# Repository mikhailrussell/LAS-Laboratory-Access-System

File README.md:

# LAS-Laboratory-Access-System-
Current PCB Version: **LAS_V2**
You can find the most recent version of the PCB under /PCB

# User Requirements
|Number/Label	|Requirement|
|----------|------------|
|UR-1	| Allow clients to book particular sessions (time and date). |
|UR-2|	Allow clients to view what the status of laboratory.
|UR-3|	Integrate access control with the current student card for identification.
|UR-4|	Provide access to clients who have been allocated the correct session.
|UR-5|	The status of benches must be physically displayed on the bench.
|UR-6|	The system must be easily scalable.
|UR-7|	The system must be cheap.

# Hardware Functional Requirements

|Number/label	|Requirements	|Acceptance Test Criteria|
|----------|------------|------------|
|FR-1	|Retrieve student's IDs from 125KHz RFID student cards.	|
|FR-2	|Connect to network wirelessly.	|
|FR-3	|Each bench must have LEDs to indicate whether the bench is available, booked or in use.|	
|FR-4	|Each node must be able to activate a 220V relay.	|
|FR-5	|Operate off 12V	|
|FR-6	|Cheap and easily scalable	|

# Software Functional Requirements

|Number/label	|Requirements	|Acceptance Test Criteria|
|----------|------------|------------|
|FR-6|	Site accessible via Wi-Fi (website accessible)	|
FR-7|	Free	|
FR-8|	Client able to book time and date	|
FR-9	|Current lab status is displayed (eg. Current tables free)	|

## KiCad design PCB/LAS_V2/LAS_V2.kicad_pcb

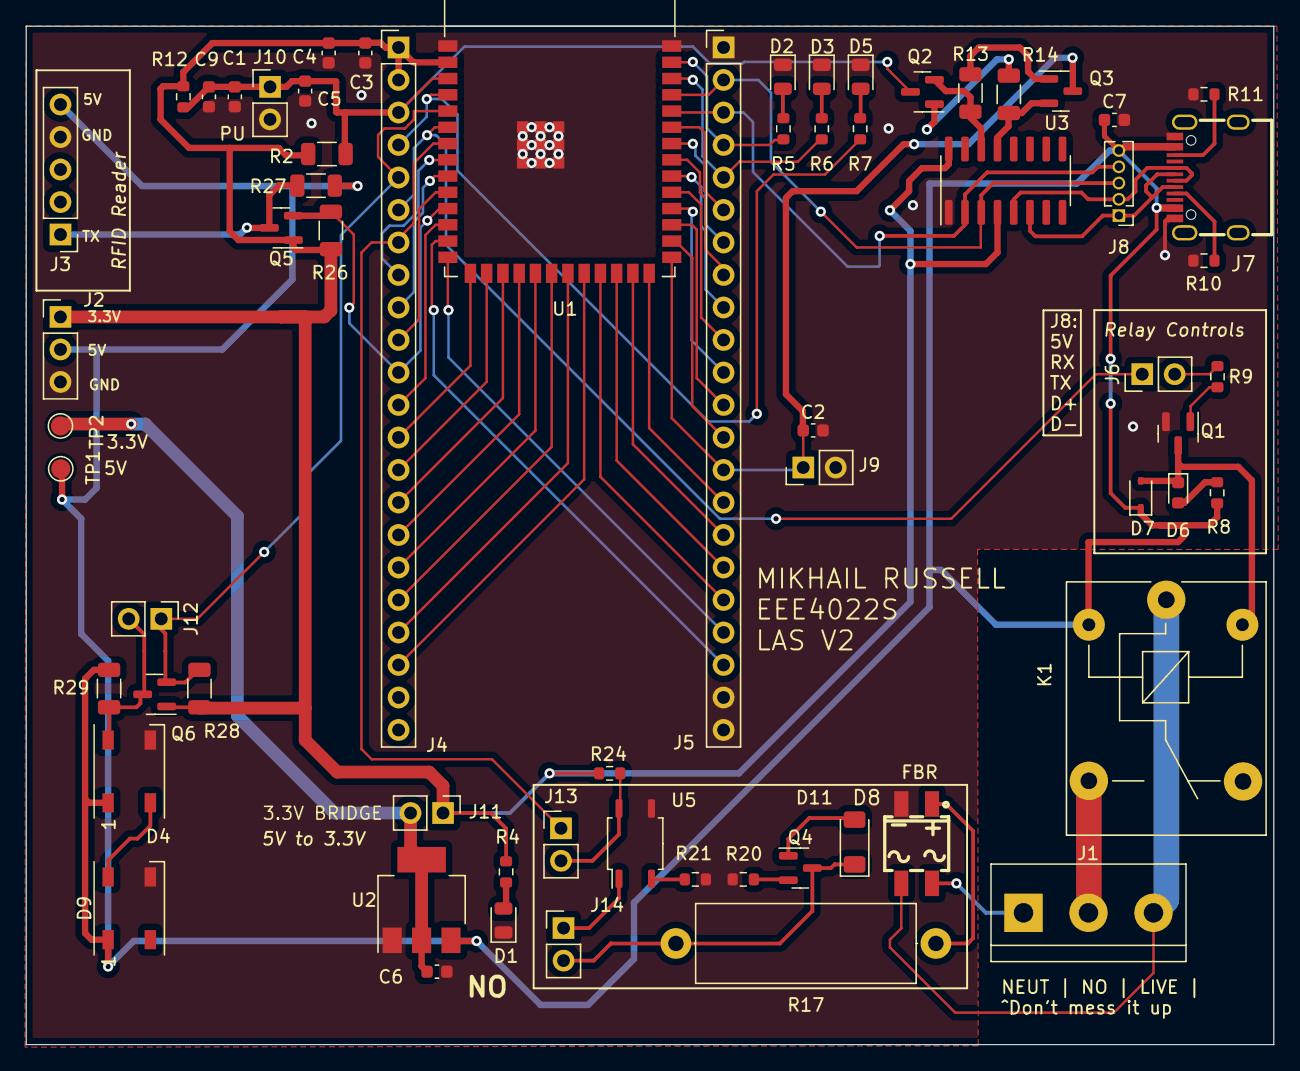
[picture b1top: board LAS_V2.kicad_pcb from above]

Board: 2 copper layers, 97.5 x 79.6 mm, 65 parts (0 on the bottom side), 70 nets.

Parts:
C1: 1uF; C_0603_1608Metric
C2, C4, C5: 0.1uF; C_0603_1608Metric
C3, C6: 10uF; C_0603_1608Metric
C7, C9: 1uF/16V (10%); C_0603_1608Metric
D1, D2: RED LED; LED_0805_2012Metric
D3: YELLOW LED; LED_0805_2012Metric
D4, D9: WS2812B; LED_WS2812B_PLCC4_5.0x5.0mm_P3.2mm
D5: GREEN LED; LED_0805_2012Metric
D6: LED; LED_0603_1608Metric
D7: 1N5819WS; D_SOD-323
D8: MB10S; MBS_L4.7-W3.8-P2.40-LS7.0-TL
D11: ZMMxx; D_MiniMELF
J1: Screw_Terminal_01x03; TerminalBlock_bornier-3_P5.08mm
J2: Conn_01x03_Pin; PinHeader_1x03_P2.54mm_Vertical
J3: Conn_01x05_Socket; PinHeader_1x05_P2.54mm_Vertical
J4, J5: Conn_01x22_Socket; PinHeader_1x22_P2.54mm_Vertical
J6, J9, J10, J11, J12, J13, J14: Conn_01x02_Pin; PinHeader_1x02_P2.54mm_Vertical
J7: USB_C_Receptacle_USB2.0; USB-C_SMD-TYPE-C-31-M-12
J8: Conn_01x05; PinHeader_1x05_P1.27mm_Vertical
K1: SRD-05VDC-SL-C; Relay_SPDT_SANYOU_SRD_Series_Form_C
Q1, Q2, Q3, Q4: MMBT2222A; SOT-23
Q5, Q6: AO3400A; SOT-23
R2, R13, R14, R26, R27, R28, R29: 10k; R_1206_3216Metric
R4, R5, R6, R7, R8, R21: 1k; R_0603_1608Metric
R9: 150; R_0603_1608Metric
R10, R11: 5.1k; R_0603_1608Metric
R12: 10k (1%); R_0603_1608Metric
R17: 47k 3W; R_Axial_DIN0617_L17.0mm_D6.0mm_P20.32mm_Horizontal
R20, R24: 2.2k; R_0603_1608Metric
TP1, TP2: TestPoint; TestPoint_Pad_D1.5mm
U1: ESP32-S3-WROOM-1
U2: AMS1117-3.3; SOT-223-3_TabPin2
U3: CH340C; SOIC-16_3.9x9.9mm_P1.27mm
U5: EL357N; SOP-4_3.8x4.1mm_P2.54mm

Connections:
/+3.3V: C3.1, C4.1, J2.1, J4.1, J4.2, J11.1, Q5.1 (G), Q6.1 (G), R2.1, R4.1, R12.1, R24.2, R26.1, R28.1, U1.2 (3V3), U3.4 (V3), U3.16 (VCC)
/AC_Mon_1: J4.7, J13.1, U1.7 (GPIO7/TOUCH7/ADC1_CH6)
/BOOT_SEL: C2.1, J5.14, J9.1, Q3.3 (C), U1.27 (GPIO0/BOOT)
/CHIP_PU: C1.1, C5.1, C9.1, J4.3, J10.1, Q2.3 (C), R2.2, R12.2, U1.3 (EN)
/DIN_3.3: J4.5, J12.1, Q6.2 (S), R28.2, U1.5 (GPIO5/TOUCH5/ADC1_CH4)
/GPIO1: J5.4, R5.1, U1.39 (GPIO1/TOUCH1/ADC1_CH0)
/GPIO2: J5.5, R6.1, U1.38 (GPIO2/TOUCH2/ADC1_CH1)
/GPIO3: J4.13, U1.15 (GPIO3/TOUCH3/ADC1_CH2)
/GPIO4: J4.4, R7.1, U1.4 (GPIO4/TOUCH4/ADC1_CH3)
/GPIO6: J4.6, J6.1, U1.6 (GPIO6/TOUCH6/ADC1_CH5)
/GPIO8: J4.12, U1.12 (GPIO8/TOUCH8/ADC1_CH7/SUBSPICS1)
/GPIO9: J4.15, U1.17 (GPIO9/TOUCH9/ADC1_CH8/FSPIHD/SUBSPIHD)
/GPIO10: J4.16, U1.18 (GPIO10/TOUCH10/ADC1_CH9/FSPICS0/FSPIIO4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)
/GPIO11: J4.17, U1.19 (GPIO11/TOUCH11/ADC2_CH0/FSPID/FSPIIO5/S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)
/GPIO12: J4.18, U1.20 (GPIO12/TOUCH12/ADC2_CH1/FSPICLK/FSPIIO6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)
/GPIO13: J4.19, U1.21 (GPIO13/TOUCH13/ADC2_CH2/FSPIQ/FSPIIO7/S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)
/GPIO14: J4.20, U1.22 (GPIO14/TOUCH14/ADC2_CH3/FSPIWP/FSPIDQS/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)
/GPIO15: J4.8, U1.8 (GPIO15/U0RTS/ADC2_CH4/XTAL_32K_P)
/GPIO16: J4.9, U1.9 (GPIO16/U0CTS/ADC2_CH5/XTAL_32K_N)
/GPIO17: J4.10, U1.10 (GPIO17/U1TXD/ADC2_CH6)
/GPIO18: J4.11, Q5.2 (S), R26.2, U1.11 (GPIO18/U1RXD/ADC2_CH7/CLK_OUT3)
/GPIO19: J5.20, U1.13 (GPIO19/U1RTS/ADC2_CH8/CLK_OUT2/USB_D-)
/GPIO20: J5.19, U1.14 (GPIO20/U1CTS/ADC2_CH9/CLK_OUT1/USB_D+)
/GPIO21: J5.18, U1.23 (GPIO21)
/GPIO35: J5.13, U1.28 (SPIIO6/GPIO35/FSPID/SUBSPID)
/GPIO36: J5.12, U1.29 (SPIIO7/GPIO36/FSPICLK/SUBSPICLK)
/GPIO37: J5.11, U1.30 (SPIDQS/GPIO37/FSPIQ/SUBSPIQ)
/GPIO38: J5.10, U1.31 (GPIO38/FSPIWP/SUBSPIWP)
/GPIO39: J5.9, U1.32 (MTCK/GPIO39/CLK_OUT3/SUBSPICS1)
/GPIO40: J5.8, U1.33 (MTDO/GPIO40/CLK_OUT2)
/GPIO41: J5.7, U1.34 (MTDI/GPIO41/CLK_OUT1)
/GPIO42: J5.6, U1.35 (MTMS/GPIO42)
/GPIO45: J5.15, U1.26 (GPIO45)
/GPIO46: J4.14, U1.16 (GPIO46)
/GPIO47: J5.17, U1.24 (GPIO47/SPICLK_P/SUBSPICLK_P_DIFF)
/GPIO48: J5.16, U1.25 (GPIO48/SPICLK_N/SUBSPICLK_N_DIFF)
/LEDs/DIN: D4.4 (DIN), J12.2, Q6.3 (D), R29.2
/LIVE: D8.3, J1.3, K1.1
/N01: J1.2, K1.3
/NEUTRAL: D8.4, J1.1
/RXD0: J5.3, J8.4, U1.36 (U0RXD/GPIO44/CLK_OUT2), U3.2 (TXD)
/TXD0: J5.2, J8.3, U1.37 (U0TXD/GPIO43/CLK_OUT1), U3.3 (RXD)
/TX_RFID: J3.1, Q5.3 (D), R27.2
/USB Interface/DTR: Q3.2 (E), R14.1, U3.13 (~DTR)
/USB Interface/RTS: Q2.2 (E), R13.1, U3.14 (~RTS)
/VCC_5V: C7.1, D4.1 (VDD), D7.1 (K), D9.1 (VDD), J2.2, J3.5, J7.A4 (VBUS), J7.A9 (VBUS), J7.B4 (VBUS), J7.B9 (VBUS), J8.5, K1.2, R8.1, R27.1, R29.1, TP1.1, U2.3 (VI)
GND: C1.2, C2.2, C3.2, C4.2, C5.2, C6.2, C7.2, C9.2, D1.1 (K), D2.1 (K), D3.1 (K), D4.3 (VSS), D5.1 (K), D8.2 (-), D9.3 (VSS), J2.3, J3.4, J5.1, J5.21, J5.22, J7.A1 (GND), J7.A12 (GND), J7.B1 (GND), J7.B12 (GND), J9.2, J10.2, Q1.2 (E), R10.2, R11.2, R20.1, R21.1, U1.1 (GND), U1.40 (GND), U1.41 (GND), U2.1 (GND), U3.1 (GND), U5.3
unnamed: D1.2 (A), R4.2
unnamed: D2.2 (A), R5.2
unnamed: D3.2 (A), R6.2
unnamed: D4.2 (DOUT), D9.4 (DIN)
unnamed: D5.2 (A), R7.2
unnamed: D6.2 (A), R8.2
unnamed: D6.1 (K), D7.2 (A), K1.5, Q1.3 (C)
unnamed: D8.1 (+), R17.1
unnamed: D11.2 (A), Q4.1 (B)
unnamed: D11.1 (K), J14.2, Q4.3 (C), R17.2
unnamed: J6.2, R9.1
unnamed: J7.A5 (CC1), R10.1
unnamed: J7.B5 (CC2), R11.1
unnamed: J7.A7 (D-), J7.B7 (D-), J8.1, U3.6 (UD-)
unnamed: J7.A6 (D+), J7.B6 (D+), J8.2, U3.5 (UD+)
unnamed: C6.1, J11.2, TP2.1, U2.2 (VO)
unnamed: J13.2, R24.1, U5.4
unnamed: J14.1, U5.1
unnamed: Q1.1 (B), R9.2
unnamed: Q2.1 (B), R14.2
unnamed: Q3.1 (B), R13.2
unnamed: Q4.2 (E), R20.2
unnamed: R21.2, U5.2

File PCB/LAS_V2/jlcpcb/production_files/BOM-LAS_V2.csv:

Comment,Designator,Footprint,LCSC
0.1uF,"C2,C4,C5",C_0603_1608Metric,C14663
1uF,"C1,C7,C9",C_0603_1608Metric,C15849
10k,"R13,R14,R2,R26,R27,R28,R29",R_1206_3216Metric,C17902
1N5819WS,D7,D_SOD-323,C191023
10uF,"C3,C6",C_0603_1608Metric,C19702
AO3400A,"Q5,Q6",SOT-23,C20917
1k,"R21,R4,R5,R6,R7,R8",R_0603_1608Metric,C21190
150,R9,R_0603_1608Metric,C22808
LED,D6,LED_0603_1608Metric,C2286
YELLOW LED,D3,LED_0805_2012Metric,C2296
GREEN LED,D5,LED_0805_2012Metric,C2297
5.1k,"R10,R11",R_0603_1608Metric,C23186
MB10S,D8,MBS_L4.7-W3.8-P2.40-LS7.0-TL,C2488
10k (1%),R12,R_0603_1608Metric,C25804
WS2812B,"D4,D9",LED_WS2812B_PLCC4_5.0x5.0mm_P3.2mm,C2843785
ESP32-S3-WROOM-1,U1,ESP32-S3-WROOM-1,C2913200
USB_C_Receptacle_USB2.0,J7,USB-C_SMD-TYPE-C-31-M-12,C2927038
EL357N,U5,SOP-4_3.8x4.1mm_P2.54mm,C29981
SRD-05VDC-SL-C,K1,Relay_SPDT_SANYOU_SRD_Series_Form_C,C35449
2.2k,"R20,R24",R_0603_1608Metric,C4190
AMS1117-3.3,U2,SOT-223-3_TabPin2,C6186
47k 3W,R17,R_Axial_DIN0617_L17.0mm_D6.0mm_P20.32mm_Horizontal,C714661
ZMMxx,D11,D_MiniMELF,C8062
RED LED,"D1,D2",LED_0805_2012Metric,C84256
CH340C,U3,SOIC-16_3.9x9.9mm_P1.27mm,C84681
MMBT2222A,"Q1,Q2,Q3,Q4",SOT-23,C8512

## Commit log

2023-08-07 Added PCB so far, no MC support
2023-08-07 Added more relay components, LEDS, Clearing Up
2023-08-07 Touch ups
2023-08-11 Added SQL code for viewing tables and such
2023-08-11 Added SQL committed
2023-08-26 installing JLB, PCB mostly done
2023-08-29 added JLBPCB part Numbers
2023-08-29 All components Placed on PCB
2023-08-29 PCB V1 complete
2023-08-30 PCBV1 done, moving onto V2
2023-08-30 Replaced components
2023-09-03 Need to redo PCB again
2023-09-03 Updated rme
2023-09-11 Final Changes to PCB, more code for gateway
2023-09-12 Added Deserialiser
2023-09-12 Recieving Json working for both gateway and Node
2023-09-14 Beginning data shortining
2023-09-17 Request from node sorted
2023-09-18 idk, just before swaping maybe
2023-09-18 Swapped around espcam and S3
2023-09-26 No clue, more gateway I think
2023-09-26 Added mesh codes
2023-09-26 added mesh I think
2023-09-26 Added Mesh node and Gateway working
2023-09-28 testing code added
2023-09-29 before testing strength
2023-10-03 Added Data, About to start testing ESP-Now
2023-10-05 ADded data and mesh tests
2023-10-28 added code fixes
2023-10-28 added Node-red info
